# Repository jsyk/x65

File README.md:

X65
====

The X65 is an ultimate computer for everyone interested in the venerable 65-series of 8-bit and 16-bit CPUs,
i.e. the 6502 and 65816. Specifically, it is built with the W65C02S or W65C816S CPU chips from Western Design Centre.
The 16-bit 65816 (W65C816S) CPU variant is the default and preferred CPU, as all screen-shots shown below were done on the 16-bit system.
The 65816 CPU powered the [Super Nintendo Entertainment System (SNES)](https://en.wikipedia.org/wiki/Super_Nintendo_Entertainment_System) 
and the [Apple IIGS](https://en.wikipedia.org/wiki/Apple_IIGS).
The older 8-bit 6502 CPU was the heart of NES, Apple I and II, many Ataris, Commodore 64, and many many more.

The design of X65 is fully open-source and open-hardware, and we also prefer to use just the open-source development tools
whenever possible. The X65 computer hardware is designed with modern electronics parts, but with a little bit of retro feel.
The computer is backward compatible with the 8-bit Commander X16 -- i.e. it can run their ROM, but since that ROM is copyrighted
and non-free, this is a no-go in the long run.
The goal is to build a fully *open* 8/16-bit system with good architecture and retro-gaming performance.

Compared with modern powerful platforms like x86, ARM or RISC-V, the small 65-series 8-bit or 16-bit system has the advantage
that one person, a software programmer or electronics designer, can fully comprehend the whole system with all details. 
There are not many abstraction layers hidden in supporting libraries or big frameworks. (In fact, there are none. It is just bare metal.) 

_Interfaces_: VGA 640x480 out, Stereo sound out (FM and PSG), PS/2 keyboard and mouse, SNES controller 2x ports,
Ethernet LAN 10/100Mpbs with RJ45, SDHC card slot, power-in 5V USB-C port, In-Circuit Debugger (ICD) over the USB-C with 
PC host software in Python and supporting JTAG-like functions for the 65xx platform (CPU step, trace, memory dump & poke).

Project web pages: http://www.x65.eu  -> currently links to http://www.jsykora.info

3D-render of the *Single-Board Computer* version:

Desktop setup with X65-SBC, PS/2 mouse and keyboard and a VGA monitor. Running `Planet X16' by David Murray with CX16 ROMs:

General Project Features:
-------------------------

* The CPU is W65C02 (8-bit) or the W65C816 (16-bit; default-preferred). The PCB supports both assembly options.
* Backward software compatibility with the [Commander X16](https://www.commanderx16.com/) computer.
  Can run unmodified CX16 ROM for testing purposes (beware: the ROMs are copyrighted non-free code!).
* Designed with components (chips) that are in production and available from normal electronics parts distributors in 2024,
  such as Mouser, Farnell, Digikey etc. We avoid obsolete parts.
* Balanced modern/retro design built around the central 65xx CPU supported by semi-ASICs (FPGAs) for system control (NORA),
  video (VERA) and audio (AURA) generation. The FPGAs are the little ones from the iCE40 series, and coded in verilog.
  These are modern takes on the "old masters'" designs with ULA, VIA, SID etc.
  *There is no hidden ARM or RISC-V doing heavy lifting in the background.*
* Free and open-source design. DIY and hobby-builders friendly. 
  Low-cost to build even in small quantities by individual hackers.

Block Diagram
---------------

Hardware Specification:
------------------------

* **CPU**: [W65C02 or W65C816](doc/cpu02vs816.md) in the QFP-44 package, running at 8MHz, supplied by 3.3V.
* **Memory**: 2MB asynchronous SRAM, common for ROM and RAM.
* **System controller** semi-ASIC, aka north-bridge, aka NORA: Lattice FPGA iCE40HX4K (TQFP-144) handles address decoding, 
  glue logic, PS/2 interfaces, in-circuit debugger and more. 
  "NORA" stands for NORth Adapter, has a similar function like the north bridge in a PC/X86 architecture.
  NORA takes care of the [memory address map](doc/mem-map.md) and hosts most of the [IO registers](doc/ioregs.md).
* Two ports for **SNES-style controllers**, handled by NORA.
* Two **PS/2 ports** for keyboard and mouse, handled by NORA. (note: we reimplement CX16 arduino code in pure hardware logic in verilog.)
* **Colour video** output through VGA connector, up to 640x480 pixels. 
  Generated by [VERA FPGA](https://github.com/X16Community/vera-module): the Video Embedded Retro Adapter, in Lattice FPGA iCE40UP5K. 
  The same is used in Commander X16.
* **Stereo audio** output through 3.5mm jack port. 
  Sound comes from two sources: FM-synthesis (OPM) by YM2151 clone [IKAOPM](https://github.com/ika-musume/IKAOPM) 
  implemented in [AURA FPGA](doc/aura_ym2151.md) (iCE40UP5K),
  and Programmable Sound Generator (PSG) available in VERA FPGA. These are digitally mixed in AURA and passed to a DAC.
  Besides the output jack connector, the sound can be also heard from a small on-board mono speaker.
* **SD-card slot** supporting SDHC cards (handled by VERA FPGA).
* **LAN 10/100Mbps** Ethernet port (RJ45) implemented by [Wiznet W6100](https://www.wiznet.io/product-item/w6100/) chip, 
  with hardware-integrated TCP/IP v4/v6 stack.
* **Real-time clock** (RTC) chip with battery backup.
* [**In-circuit debugger**](doc/icd.md) (ICD) integrated with NORA and accessible over the device USB-C port from a host PC
  running Linux or Windows. The ICD can write all permanent (SPI-Flash) memories in the system, 
  even in a totally empty / bricked state. PC host software is written in Python and should be portable to other 
  fruitful systems besides Linux and Windows.
  Together with NORA the ICD supports JTAG-like functions like memory poke/dump, CPU stop/step, instruction
  trace buffer, interrupt forcing/blocking etc.
* **Power input** 5V from a standard USB Type-C device port.
  The X65 computer can be powered from a normal host-PC USB port (for development with ICD), 
  or runs standalone from a common Mains/USB phone charger with just 5V output.
* Single-board PCB 180x100mm, 4-layers.

Hardware Photos:
----------------

Overview photos (2024/02) - Single-Board version:

**SBC Front view photo**:

**SBC Rear view photo**:

**SBC Top view with labels**:

Engineering testing samples, hand-assembled:

Demo Software Screen Photos
----------------------------

Running Commander X16 ROM and BASIC program (compatibility testing only, not allowed in production use due to a proprietary license):

**BAD METAL** demo from CX16:

**CALLIOPE** music player from CX16:

**Crazy Boulders**, a CX16 game by Dušan Štrakl:

**Crazy Lander**, a CX16 game by Dušan Štrakl:

**Crazy Pong**, a CX16 game by Dušan Štrakl:

**Planet X16**, a CX16 game by David Murray:

[**Integrated In-Circuit Debugger**](doc/icd.md) can live-trace the CPU from a Linux PC over the USB:

Structure of the GIT repository:
---------------------------------

* `doc' --> documentation
* `fpga-aura' --> verilog code for the AURA FPGA (Audio) with referenced IKAOPM sources.
* `fpga-nora' --> verilog code for the NORA FPGA on the motherboard.
* `fpga-vera' --> VERA FPGA bitstream (100% derived from https://github.com/fvdhoef/vera-module)
* `pcb' --> hardware projects in Kicad:
  - `mobo-rev01' --> Motherboard rev01 - OBSOLETE
  - `vabo-rev01' --> Video/Audio board rev01 - OBSOLETE
  - `x65-sbc-revA1' --> *Single-Board computer*
* `x65prog' --> linux software to program the on-board SPI flash memories from a host Linux PC via the USB link.
* `x65pyhost' --> python scripts for accessing/debugging the X65 from a host PC via the USB link.

Schematics in PDF:
------------------

**SBC Revision A1:**

* [X65-SBC, revA1 - PDF scm](pcb/x65-sbc-revA1/x65-sbc-revA1.pdf)

**SBC Revision B1:**

* [X65-SBC, revB1 - PDF scm](pcb/x65-sbc-revB1/x65-sbc-revB1.pdf)

Software:
-----------

The X65 is software-backwards-compatible with the *Commander X16*. 
It means the X65 could run unmodified CX16 ROM and programs, excluding programs depending on some of the hardware features 
in CX16 that are not supported here: cartridges, Commodore IEC port.
However, the CX16 ROM is a **proprietary**, non-open-source and non-free, piece of software created by Commodore
and (somehow) licensed to the CX16 creators. *The licensees do not wish that the ROM runs on any other HW than their own.*
Therefore, I could not recommend running that ROM on the X65 computer.

Presently I am not decided which operating system or runtime shell would be the best / easiest to port to X65.
There some existing systems that could be ported here, for example:

* [MEGA65 OPEN-ROMs](https://github.com/MEGA65/open-roms) (true free open-source sw),
* [FastBasic](https://github.com/dmsc/fastbasic)
* [GeckOS](http://www.6502.org/users/andre/osa/index.html)
* ...

Random Questions & Answers
---------------------------

**Why was this project started?**

This project started in March 2023 when I saw a prototype of Commander X16 in one of the youtube videos
of the 8-bit guy, David Murray. I immediately wanted to play with it but at the time his project was not released to the public,
the hardware could not be bought. So I decided to build one myself, based on public information available
about the CX16. And at the same time I was not too pleased with the architecture and implementation
of the CX16, not satisfied with many design choices they did. 
Consequently, my X65 tries to improve in many areas while being software-compatible.

**What is the relation to *Commander X16* and its authors?**

I have no relation or contact to the authors of Commander X16.
The public discussion forums for CX16 on discord and reddit have the policy that any discussion or mention of any
*clones* of CX16 is forbidden. 
While I find this policy strange for a community project, I respect it.
Therefore I do not tell the guys about the X65 project.

**What is the license of X65 project? Which copyrighted material was used?**

I used publicly available information on wikipedia and in the X16Community's public forums and repositories to reconstruct the CX16 architecture.
I don't have access to the schematics of X16, and I don't own that computer and never seen it in person.
My analysis of the CX16 architecture is available in the file [cx16.md](doc/cx16.md).
The [VERA](https://github.com/fvdhoef/vera-module) FPGA by Frank van den Hoef, also [here](https://github.com/X16Community/vera-module),
 was reused as-is and it is covered by the open-source MIT license.
The AURA FPGA is based on [IKAOPM](https://github.com/ika-musume/IKAOPM), a YM2151 reconstruction in verilog, and it is covered by the BSD 2-Clause License.
All my documents and designs in this repository are covered by the [MIT license](LICENSE).
The restricted CX16 ROMs are not part of this repository.

**What are the advantages of X65-SBC over other retro-modern-computers?**

The X65-SBC is a complete computer system with ports for a keyboard and a mouse, a high-resolution VGA output (128kB Video-RAM), 
and high-quality stereo audio capable of PCM, PSG (Programmable Sound Generator) and FM-synthesis sound generation.
Compared with other 65xx-based computers, we support the 16-bit processor 65C816 which is capable of direct addressing of 
up to 16MB of RAM; the X65-SBC includes 2MB of fast SRAM by default.
System controller is realized by NORA FPGA (lattice ice40hx4k) and potentially allows experimenting with additional
features like virtual memory or mathematical coprocessors.
The hardware supports direct programming of FPGA bitstreams via the USB-C port from a Linux PC; in a way the X65-SBC
is a self-contained FPGA development platform.
The design is fully open-source.

**Where can I get the hardware?**

As all relevant HW design data is available in this repository, anybody with appropriate electronics knowledge 
and a lab can build own copy of the X65-SBC hardware.
The cost of electronics components is around 130 EUR, plus the cost of board assembly (which can be done DIY if necessary).
Maybe in the future I can run a very small series build for interested programmers and "hackers". 
However, as these builds surely will not have the requisite FCC / UL / CE approvals (that costs addional money), 
the resulting devices could only be used in a lab for development purposes by knowledgable users.
I am open to the possibility that some company decides to commercionalize X65-SBC as a sellable product and puts it on the market :-)

**Is there an emulator for PC?**

Presently an emulator is not developed yet.
It could be done perhaps based on the [CX16 emulator](https://github.com/commanderx16/x16-emulator); 
the CPU emulation has to be extended to 65C816 and new features (registers)
available in NORA and in W6100 (ethernet interface) need be implemented.

Contact
--------

**Jaroslav Sýkora**
- Personal: http://www.jsykora.info,
- GIT account: https://github.com/jsyk,
- Mastodon: https://oldbytes.space/@jarda,
- (Physically in the Czech Republic.)

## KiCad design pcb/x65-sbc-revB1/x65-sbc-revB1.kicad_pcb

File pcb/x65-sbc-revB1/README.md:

X65-SBC-rev.B1
================

X65 Single-Board Computer, schematic & PCB revision B1.

!! WORK IN PROGRESS !!
=======================

I restarted changes to revB1 on 04/2024 with the following goals:
* fix remaining issues (SDC power, ESD, see below)
* optimize for machine assembly

To-Be-Done changes from rev.A1 to rev.B1
-------------------------------------------
* add power switch for SDC +3.3V, add digital lines disconnect
    - probably AP2191D ?
* change ESD protection
* change decoupling caps
* move speaker connector
* ...??? see pdf

Implemented changes from rev.A1 to rev.B1
-------------------------------------------
* change green LED resistors to 2k7 (although this depends on LED).
* Remove D504 (USB ESD): the SP0503 is not suitable!
* Add 5V and +3.3V pins to J601 internal mem.bus connector.
* Changed AURA FPGA footprint to the smaller EP pad (now the footprint is the same as VERA)

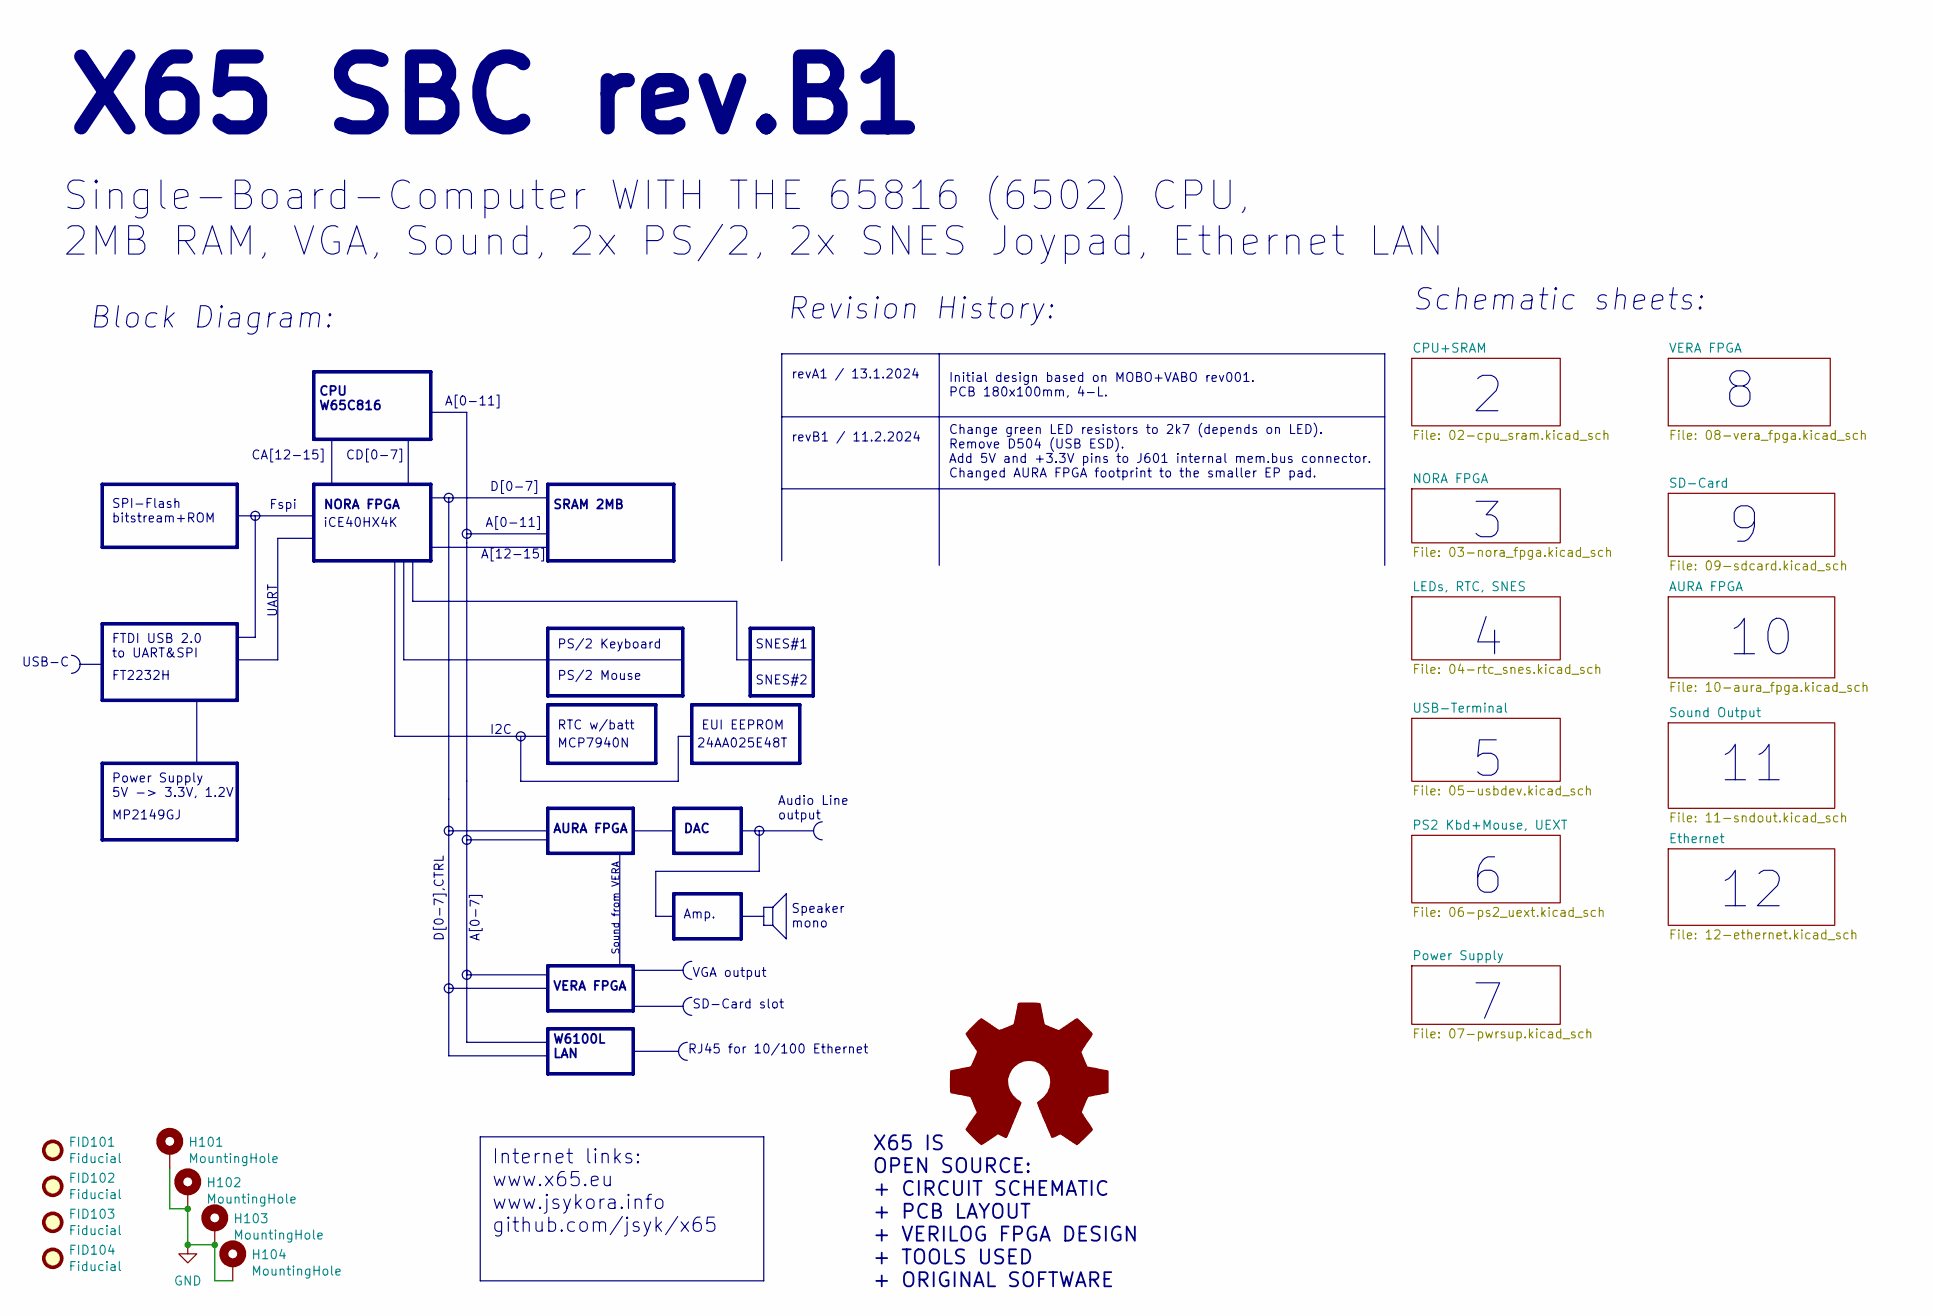
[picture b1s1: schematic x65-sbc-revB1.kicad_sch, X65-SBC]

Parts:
FID101, FID102, FID103, FID104: Fiducial; Fiducial_1mm_Mask2mm
H101, H102, H103, H104: MountingHole; MountingHole_3.2mm_M3_Pad
SYM101: Logo_Open_Hardware_Large; OSHW-Logo2_7.3x6mm_SilkScreen

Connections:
GND: H101.1, H102.1, H103.1, H104.1; also elsewhere on the board

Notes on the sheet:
Internet links: www.x65.eu www.jsykora.info github.com/jsyk/x65
Amp.
Block Diagram:
Initial design based on MOBO+VABO rev001. PCB 180x100mm, 4-L.
Schematic sheets:
MCP7940N
CA[12-15]
RJ45 for 10/100 Ethernet
CPU W65C816
A[12-15]
Single-Board-Computer WITH THE 65816 (6502) CPU, 2MB RAM, VGA, Sound, 2x PS/2, 2x SNES Joypad, Ethernet LAN
revB1 / 11.2.2024
A[0-11]
CD[0-7]
W6100L LAN
SNES#2
Sound from VERA
FT2232H
NORA FPGA
Fspi
X65 SBC rev.B1
SD-Card slot
Revision History:
EUI EEPROM
PS/2 Keyboard
revA1 / 13.1.2024
VERA FPGA
DAC
I2C
Speaker mono
UART
iCE40HX4K
VGA output
Power Supply 5V -> 3.3V, 1.2V
SPI-Flash bitstream+ROM
X65 IS OPEN SOURCE: + CIRCUIT SCHEMATIC + PCB LAYOUT + VERILOG FPGA DESIGN + TOOLS USED + ORIGINAL SOFTWARE
Change green LED resistors to 2k7 (depends on LED). Remove D504 (USB ESD). Add 5V and +3.3V pins to J601 internal mem.bus connector. Changed AURA FPGA footprint to the smaller EP pad.
MP2149GJ
RTC w/batt
USB-C

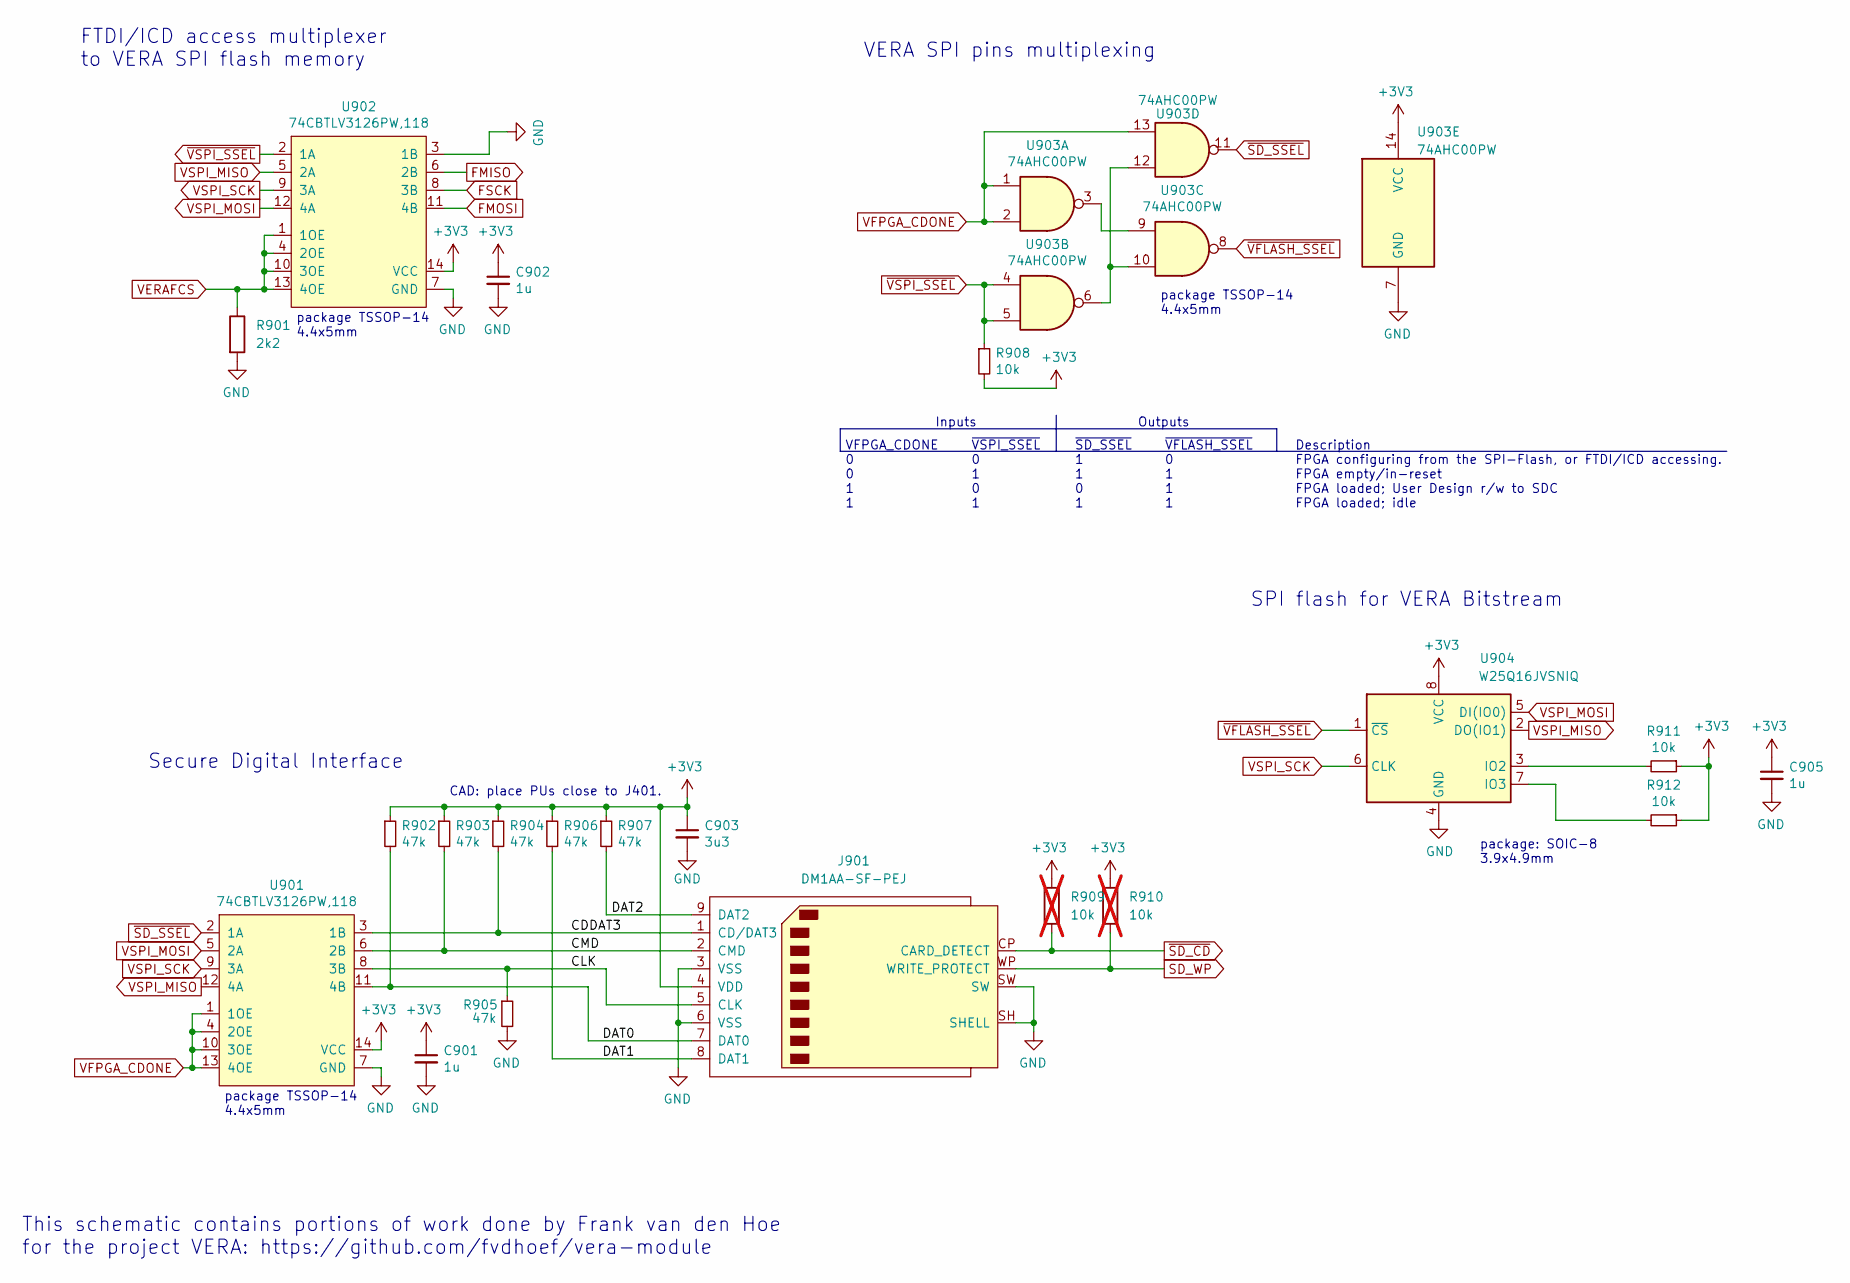
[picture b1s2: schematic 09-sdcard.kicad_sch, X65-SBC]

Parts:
C901, C902, C905: 1u; C_0603_1608Metric_Pad1.08x0.95mm_HandSolder
C903: 3u3; C_0603_1608Metric_Pad1.08x0.95mm_HandSolder
J901: DM1AA-SF-PEJ; SD_Hirose_DM1AA_SF_PEJ82
R901: 2k2; R_0603_1608Metric_Pad0.98x0.95mm_HandSolder
R902, R903, R904, R905, R906, R907: 47k; R_0603_1608Metric_Pad0.98x0.95mm_HandSolder
R908, R911, R912: 10k; R_0603_1608Metric_Pad0.98x0.95mm_HandSolder
R909, R910: 10k; R_0603_1608Metric_Pad0.98x0.95mm_HandSolder; not fitted
U901, U902: 74CBTLV3126PW,118; TSSOP-14_4.4x5mm_P0.65mm
U903: 74AHC00PW; TSSOP-14_4.4x5mm_P0.65mm
U904: W25Q16JVSNIQ; SOIC-8_3.9x4.9mm_P1.27mm

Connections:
+3V3: C901.1, C902.1, C903.1, C905.1, J901.4 (VDD), R902.1, R903.1, R904.1, R906.1, R907.1, R908.2, R909.1, R910.1, R911.1, R912.1, U901.14 (VCC), U902.14 (VCC), U903.14 (VCC), U904.8 (VCC); also elsewhere on the board
/SD-Card/CDDAT3: J901.1 (CD/DAT3), R904.2, U901.3 (1B)
/SD-Card/CLK: J901.5 (CLK), R905.1, U901.8 (3B)
/SD-Card/CMD: J901.2 (CMD), R903.2, U901.6 (2B)
/SD-Card/DAT0: J901.7 (DAT0), R902.2, U901.11 (4B)
/SD-Card/DAT1: J901.8 (DAT1), R906.2
/SD-Card/DAT2: J901.9 (DAT2), R907.2
FMISO: U902.6 (2B); also elsewhere on the board
FMOSI: U902.11 (4B); also elsewhere on the board
FSCK: U902.8 (3B); also elsewhere on the board
GND: C901.2, C902.2, C903.2, C905.2, J901.3 (VSS), J901.6 (VSS), J901.SH (SHELL), J901.SW, R901.2, R905.2, U901.7 (GND), U902.3 (1B), U902.7 (GND), U903.7 (GND), U904.4 (GND); also elsewhere on the board
unnamed: U903.3, U903.9
unnamed: U903.6, U903.10, U903.12
unnamed: R911.2, U904.3 (IO2)
unnamed: R912.2, U904.7 (IO3)
SD_WP: J901.WP (WRITE_PROTECT), R910.2; also elsewhere on the board
VERAFCS: R901.1, U902.1 (1OE), U902.4 (2OE), U902.10 (3OE), U902.13 (4OE); also elsewhere on the board
VFPGA_CDONE: U901.1 (1OE), U901.4 (2OE), U901.10 (3OE), U901.13 (4OE), U903.1, U903.2, U903.13; also elsewhere on the board
VSPI_MISO: U901.12 (4A), U902.5 (2A), U904.2 (DO(IO1)); also elsewhere on the board
VSPI_MOSI: U901.5 (2A), U902.12 (4A), U904.5 (DI(IO0)); also elsewhere on the board
VSPI_SCK: U901.9 (3A), U902.9 (3A), U904.6 (CLK); also elsewhere on the board
~SD_CD: J901.CP (CARD_DETECT), R909.2; also elsewhere on the board
~SD_SSEL: U901.2 (1A), U903.11; also elsewhere on the board
~VFLASH_SSEL: U903.8, U904.1 (~CS)
~VSPI_SSEL: R908.1, U902.2 (1A), U903.4, U903.5; also elsewhere on the board

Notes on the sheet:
~{SD_SSEL} 1 1 0 1
This schematic contains portions of work done by Frank van den Hoe for the project VERA: https://github.com/fvdhoef/vera-module
~{VFLASH_SSEL} 0 1 1 1
Inputs
VFPGA_CDONE 0 0 1 1
package TSSOP-14 4.4x5mm
CAD: place PUs close to J401.
Outputs
package: SOIC-8 3.9x4.9mm
FTDI/ICD access multiplexer to VERA SPI flash memory
Description FPGA configuring from the SPI-Flash, or FTDI/ICD accessing. FPGA empty/in-reset FPGA loaded; User Design r/w to SDC FPGA loaded; idle
~{VSPI_SSEL} 0 1 0 1
Secure Digital Interface
SPI flash for VERA Bitstream
VERA SPI pins multiplexing

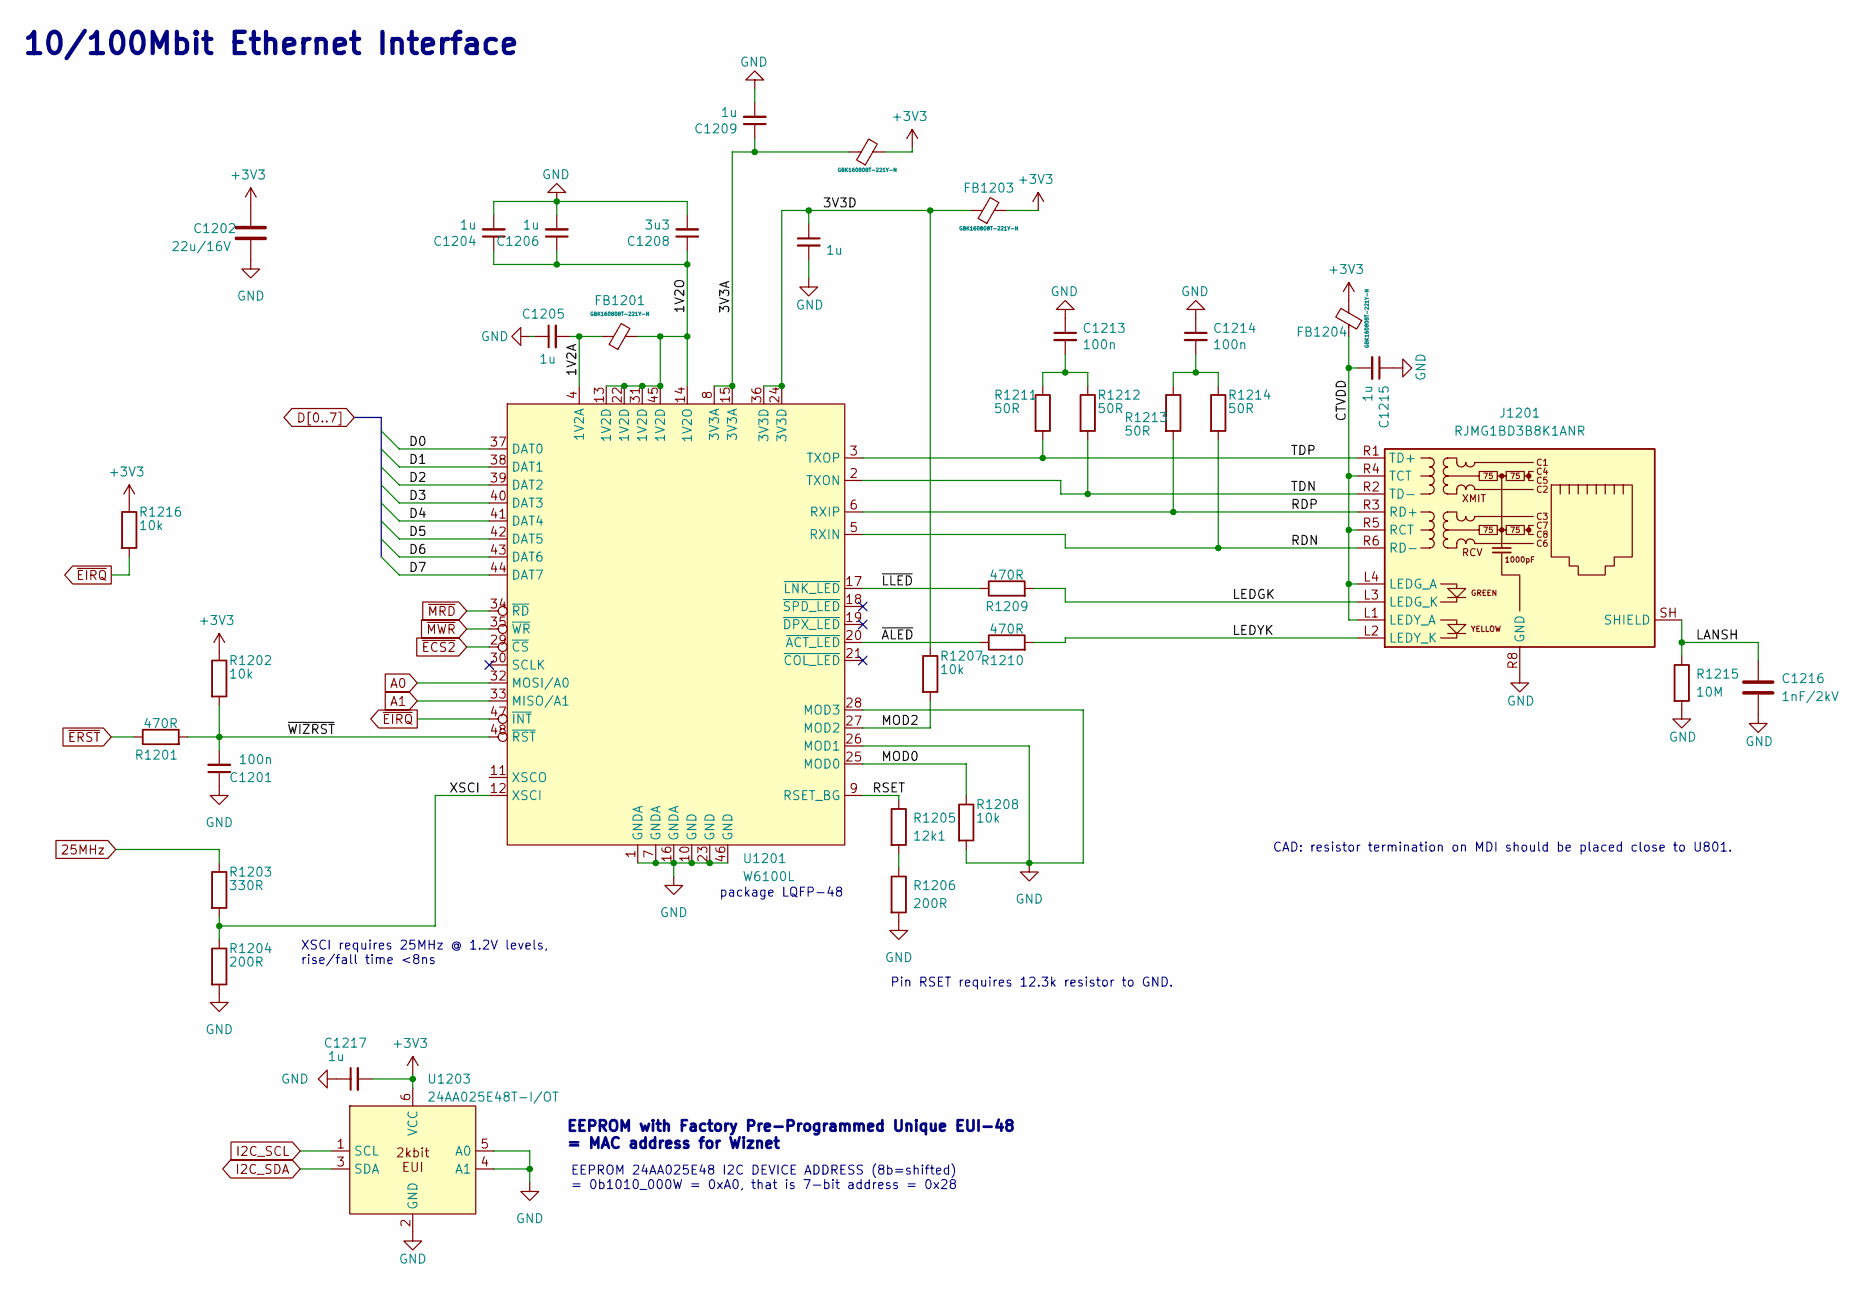
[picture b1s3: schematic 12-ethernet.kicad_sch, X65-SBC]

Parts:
C1201, C1213, C1214: 100n; C_0603_1608Metric_Pad1.08x0.95mm_HandSolder
C1202: 22u/16V; C_0805_2012Metric_Pad1.18x1.45mm_HandSolder
C1204, C1205, C1206, C1209, C1210, C1215, C1217: 1u; C_0603_1608Metric_Pad1.08x0.95mm_HandSolder
C1208: 3u3; C_0603_1608Metric_Pad1.08x0.95mm_HandSolder
C1216: 1nF/2kV; C_1206_3216Metric_Pad1.33x1.80mm_HandSolder
FB1201, FB1202, FB1203, FB1204: GBK160808T-221Y-N; R_0603_1608Metric_Pad0.98x0.95mm_HandSolder
J1201: RJMG1BD3B8K1ANR; RJ45_Amphenol_RJMG1BD3B8K1ANR
R1201, R1209, R1210: 470R; R_0603_1608Metric_Pad0.98x0.95mm_HandSolder
R1202, R1207, R1208, R1216: 10k; R_0603_1608Metric_Pad0.98x0.95mm_HandSolder
R1203: 330R; R_0603_1608Metric_Pad0.98x0.95mm_HandSolder
R1204, R1206: 200R; R_0603_1608Metric_Pad0.98x0.95mm_HandSolder
R1205: 12k1; R_0603_1608Metric_Pad0.98x0.95mm_HandSolder
R1211, R1212, R1213, R1214: 50R; R_0603_1608Metric_Pad0.98x0.95mm_HandSolder
R1215: 10M; R_2512_6332Metric_Pad1.40x3.35mm_HandSolder
U1201: W6100L; LQFP-48_7x7mm_P0.5mm
U1203: 24AA025E48T-I/OT; SOT-23-6_Handsoldering

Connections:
25MHz: R1203.1; also elsewhere on the board
+3V3: C1202.2, C1217.2, FB1202.2, FB1203.2, FB1204.2, R1202.1, R1216.1, U1203.6 (VCC); also elsewhere on the board
/Ethernet/1V2A: C1205.2, FB1201.1, U1201.4 (1V2A)
/Ethernet/1V2O: C1204.1, C1206.1, C1208.1, FB1201.2, U1201.13 (1V2D), U1201.14 (1V2O), U1201.22 (1V2D), U1201.31 (1V2D), U1201.45 (1V2D)
/Ethernet/3V3A: C1209.1, FB1202.1, U1201.8 (3V3A), U1201.15 (3V3A)
/Ethernet/3V3D: C1210.1, FB1203.1, R1207.1, U1201.24 (3V3D), U1201.36 (3V3D)
/Ethernet/CTVDD: C1215.2, FB1204.1, J1201.L1 (LEDY_A), J1201.L4 (LEDG_A), J1201.R4 (TCT), J1201.R5 (RCT)
/Ethernet/LANSH: C1216.1, J1201.SH (SHIELD), R1215.1
/Ethernet/LEDGK: J1201.L3 (LEDG_K), R1209.2
/Ethernet/LEDYK: J1201.L2 (LEDY_K), R1210.2
/Ethernet/MOD0: R1208.1, U1201.25 (MOD0)
/Ethernet/MOD2: R1207.2, U1201.27 (MOD2)
/Ethernet/RDN: J1201.R6 (RD-), R1214.2, U1201.5 (RXIN)
/Ethernet/RDP: J1201.R3 (RD+), R1213.2, U1201.6 (RXIP)
/Ethernet/RSET: R1205.1, U1201.9 (RSET_BG)
/Ethernet/TDN: J1201.R2 (TD-), R1212.2, U1201.2 (TXON)
/Ethernet/TDP: J1201.R1 (TD+), R1211.2, U1201.3 (TXOP)
/Ethernet/XSCI: R1203.2, R1204.1, U1201.12 (XSCI)
/Ethernet/~ALED: R1210.1, U1201.20 (~ACT_LED)
/Ethernet/~LLED: R1209.1, U1201.17 (~LNK_LED)
/Ethernet/~WIZRST: C1201.2, R1201.2, R1202.2, U1201.48 (~RST)
A0: U1201.32 (MOSI/A0); also elsewhere on the board
A1: U1201.33 (MISO/A1); also elsewhere on the board
D0: U1201.37 (DAT0); also elsewhere on the board
D1: U1201.38 (DAT1); also elsewhere on the board
D2: U1201.39 (DAT2); also elsewhere on the board
D3: U1201.40 (DAT3); also elsewhere on the board
D4: U1201.41 (DAT4); also elsewhere on the board
D5: U1201.42 (DAT5); also elsewhere on the board
D6: U1201.43 (DAT6); also elsewhere on the board
D7: U1201.44 (DAT7); also elsewhere on the board
GND: C1201.1, C1202.1, C1204.2, C1205.1, C1206.2, C1208.2, C1209.2, C1210.2, C1213.1, C1214.1, C1215.1, C1216.2, C1217.1, J1201.R8 (GND), R1204.2, R1206.2, R1208.2, R1215.2, U1201.1 (GNDA), U1201.7 (GNDA), U1201.10 (GND), U1201.16 (GNDA), U1201.23 (GND), U1201.26 (MOD1), U1201.28 (MOD3), U1201.46 (GND), U1203.2 (GND), U1203.4 (A1), U1203.5 (A0); also elsewhere on the board
I2C_SCL: U1203.1 (SCL); also elsewhere on the board
I2C_SDA: U1203.3 (SDA); also elsewhere on the board
unnamed: C1213.2, R1211.1, R1212.1
unnamed: C1214.2, R1213.1, R1214.1
unnamed: R1205.2, R1206.1
~ECS2: U1201.29 (~CS); also elsewhere on the board
~EIRQ: R1216.2, U1201.47 (~INT); also elsewhere on the board
~ERST: R1201.1; also elsewhere on the board
~MRD: U1201.34 (~RD); also elsewhere on the board
~MWR: U1201.35 (~WR); also elsewhere on the board

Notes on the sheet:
EEPROM 24AA025E48 I2C DEVICE ADDRESS (8b=shifted) = 0b1010_000W = 0xA0, that is 7-bit address = 0x28
package LQFP-48
CAD: resistor termination on MDI should be placed close to U801.
XSCI requires 25MHz @ 1.2V levels, rise/fall time <8ns
Pin RSET requires 12.3k resistor to GND.
10/100Mbit Ethernet Interface
EEPROM with Factory Pre-Programmed Unique EUI-48 = MAC address for Wiznet

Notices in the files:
x65prog/x65prog.c:
Copyright (C) 2015  Clifford Wolf <clifford@clifford.at>
Copyright (C) 2018  Piotr Esden-Tempski <piotr@esden.net>
